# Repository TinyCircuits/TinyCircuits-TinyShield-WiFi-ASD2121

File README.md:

# TinyCircuits TinyShield WiFi Board
# ASD2121 Rev2

These are the design files for the TinyCircuits ASD2121 Rev 2 PCB.  This is a TinyShield board that has a TI CC3000 WiFi module, local power supply and level shifters to connect between the TinyDuino and the WiFi Module. 

Format is in Cadsoft Eagle format - Eagle version 6.2 was used for the original design.

For more infomation on this, check out the product page at Tiny-Circuits.com:  https://tiny-circuits.com/tiny-shield-wifi.html

#License:

Design by TinyCircuits.
All design files are released under the Creative Commons Attribution Share-Alike 3.0 License, see the following link for details: http://creativecommons.org/licenses/by-sa/3.0

All text above must be included in any redistribution or derived design

This project uses designs and concepts developed as part of the Arduino project and the LilyPad project.  The TinyCircuits design files themselves (schematics, PCB and libraries) are not directly derived from these works' design files and have been created new, however the concepts and basic architecture behind the TinyDuino and TinyLily products are derived and we thank the hard work of the organizations below for their contributions to open-source hardware:
  
Original Arduino Uno Design by Team Arduino

LilyPad Arduino Design by Leah Buechley and Sparkfun Electronics

Please support the open-source hardware community

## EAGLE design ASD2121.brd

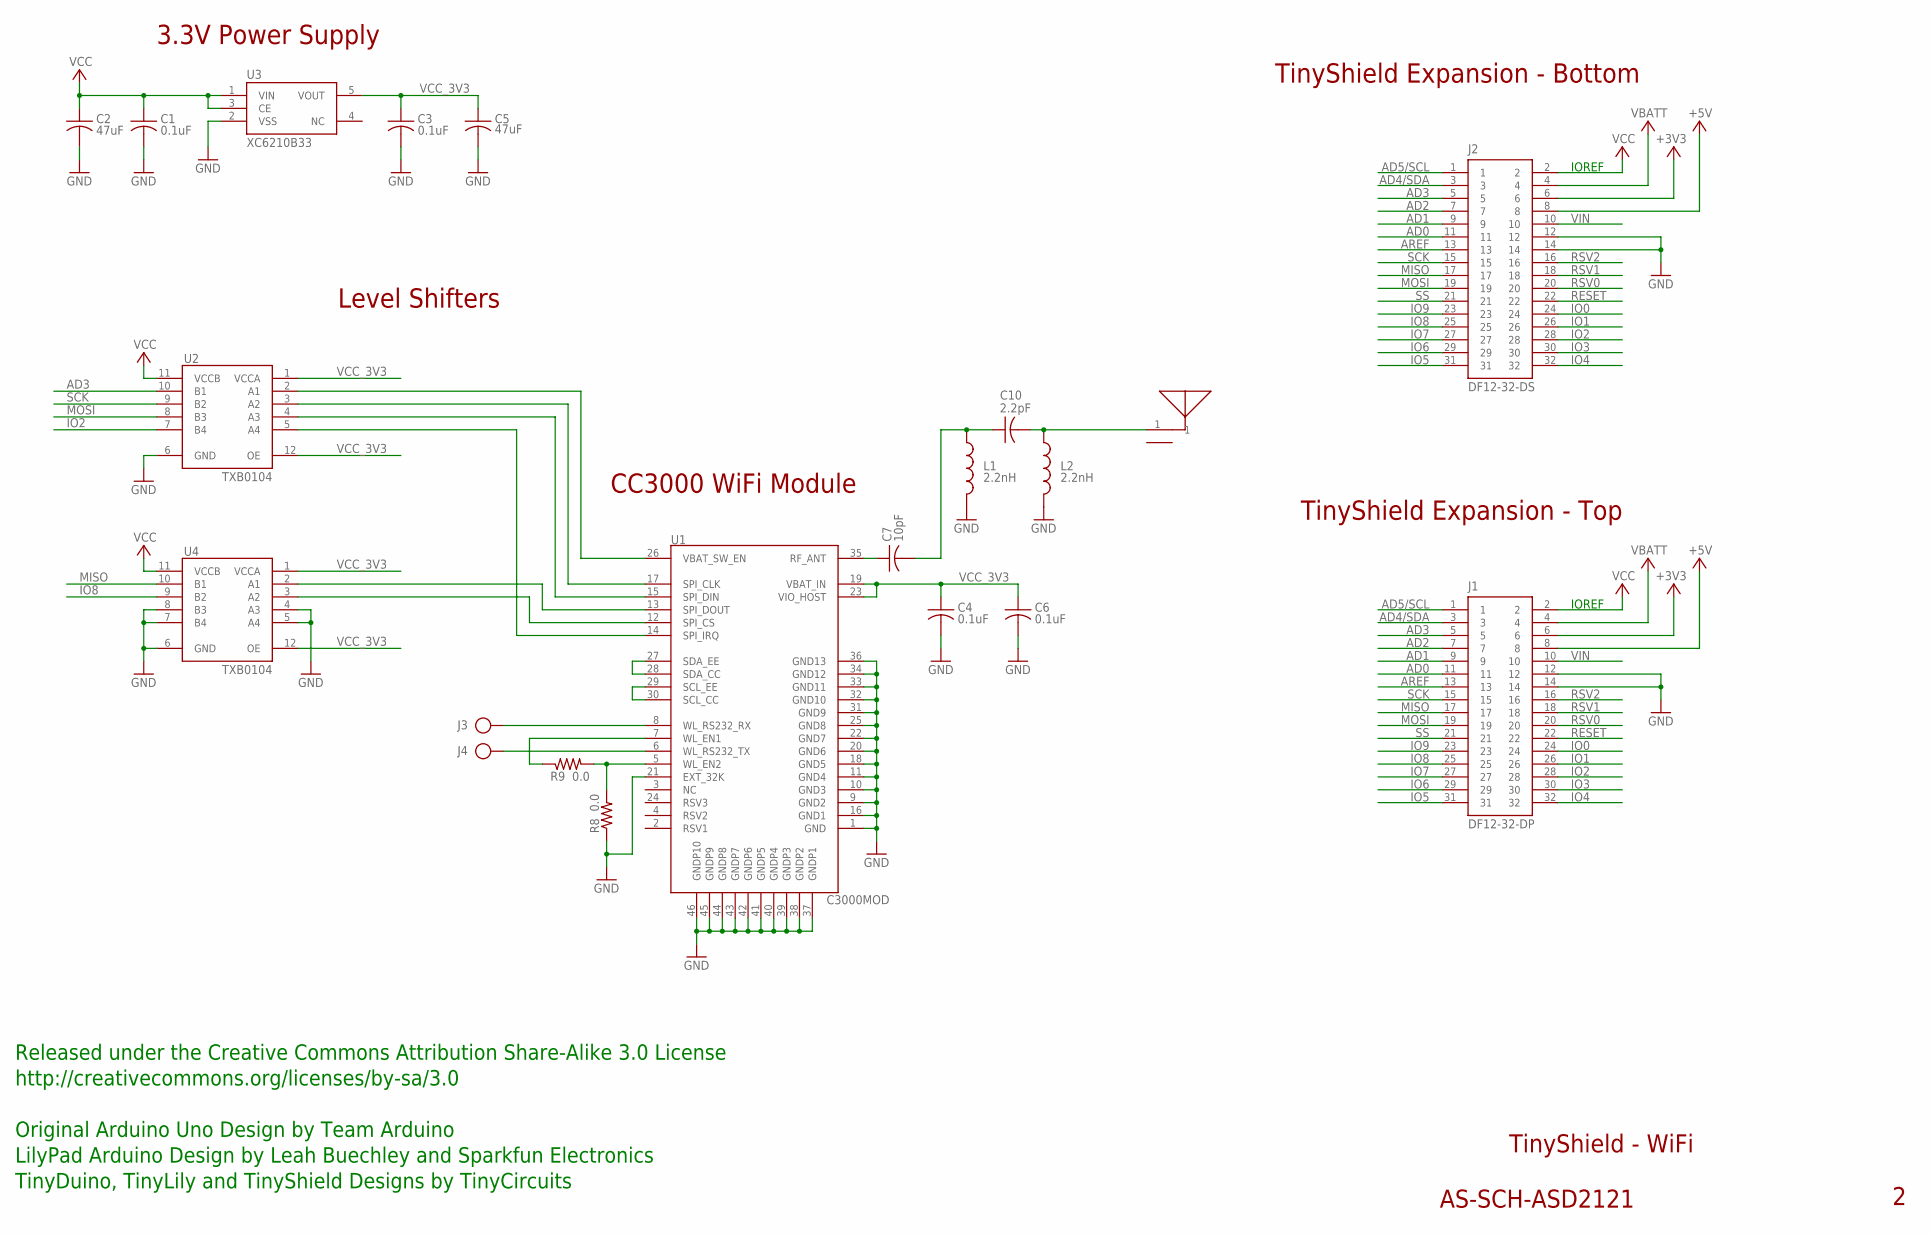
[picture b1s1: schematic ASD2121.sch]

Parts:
ANT1: AS-ITM-00082; 2G4_ANT
C1, C3, C4, C6: 0.1uF; C0402; PARTNO AS-ITM-00008
C2: 47uF; C1206; PARTNUM AS-ITM-00049
C5: 47uF; C1206
C7: 10pF; C0402; PARTNO AS-ITM-00107
C10: 2.2pF; C0402; PARTNO AS-ITM-00106
J1: DF12-32-DP; PARTNO AS-ITM-00015
J2: DF12-32-DS; PARTNO AS-ITM-00012
J3, J4: PIN_1X.1"SQ_PAD; TEST_POINT
L1, L2: 2.2nH; C0402; PARTNO AS-ITM-00108
R8: 0.0; 0402
R9: 0.0; 0402_SHORT
U1: C3000MOD; CC3000MOD
U2, U4: TXB0104; UQFN-12
U3: XC6210B33; SOT-25

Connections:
+3V3: J1.6, J2.6
+5V: J1.8, J2.8
AD0: J1.11, J2.11
AD1: J1.9, J2.9
AD2: J1.7, J2.7
AD3: J1.5, J2.5, U2.10 (B1)
AD4/SDA: J1.3, J2.3
AD5/SCL: J1.1, J2.1
AREF: J1.13, J2.13
GND: C1.2, C2.2, C3.2, C4.2, C5.2, C6.2, J1.12, J1.14, J2.12, J2.14, L1.2, L2.2, R8.1, U1.1 (GND), U1.9 (GND2), U1.10 (GND3), U1.11 (GND4), U1.16 (GND1), U1.18 (GND5), U1.20 (GND6), U1.21 (EXT_32K), U1.22 (GND7), U1.25 (GND8), U1.31 (GND9), U1.32 (GND10), U1.33 (GND11), U1.34 (GND12), U1.36 (GND13), U1.37 (GNDP1), U1.38 (GNDP2), U1.39 (GNDP3), U1.40 (GNDP4), U1.41 (GNDP5), U1.42 (GNDP6), U1.43 (GNDP7), U1.44 (GNDP8), U1.45 (GNDP9), U1.46 (GNDP10), U2.6 (GND), U3.2 (VSS), U4.4 (A3), U4.5 (A4), U4.6 (GND), U4.7 (B4), U4.8 (B3)
IO0: J1.24, J2.24
IO1: J1.26, J2.26
IO2: J1.28, J2.28, U2.7 (B4)
IO3: J1.30, J2.30
IO4: J1.32, J2.32
IO5: J1.31, J2.31
IO6: J1.29, J2.29
IO7: J1.27, J2.27
IO8: J1.25, J2.25, U4.9 (B2)
IO9: J1.23, J2.23
MISO: J1.17, J2.17, U4.10 (B1)
MOSI: J1.19, J2.19, U2.8 (B3)
unnamed: U1.29 (SCL_EE), U1.30 (SCL_CC)
unnamed: U1.27 (SDA_EE), U1.28 (SDA_CC)
unnamed: U1.14 (SPI_IRQ), U2.5 (A4)
unnamed: U1.12 (SPI_CS), U4.3 (A2)
unnamed: J3.P$1, U1.8 (WL_RS232_RX)
unnamed: U1.13 (SPI_DOUT), U4.2 (A1)
unnamed: U1.15 (SPI_DIN), U2.4 (A3)
unnamed: J4.P$1, U1.6 (WL_RS232_TX)
unnamed: R8.2, R9.2, U1.5 (WL_EN2)
unnamed: R9.1, U1.7 (WL_EN1)
unnamed: U1.17 (SPI_CLK), U2.3 (A2)
unnamed: U1.26 (VBAT_SW_EN), U2.2 (A1)
unnamed: C7.1, U1.35 (RF_ANT)
unnamed: C7.2, C10.1, L1.1
unnamed: ANT1.1, C10.2, L2.1
RESET: J1.22, J2.22
RSV0: J1.20, J2.20
RSV1: J1.18, J2.18
RSV2: J1.16, J2.16
SCK: J1.15, J2.15, U2.9 (B2)
SS: J1.21, J2.21
VBATT: J1.4, J2.4
VCC: C1.1, C2.1, J1.2, J2.2, U2.11 (VCCB), U3.1 (VIN), U3.3 (CE), U4.11 (VCCB)
VCC_3V3: C3.1, C4.1, C5.1, C6.1, U1.19 (VBAT_IN), U1.23 (VIO_HOST), U2.1 (VCCA), U2.12 (OE), U3.5 (VOUT), U4.1 (VCCA), U4.12 (OE)
VIN: J1.10, J2.10

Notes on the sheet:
TinyShield Expansion - Bottom
TinyShield - WiFi
AS-SCH-ASD2121
TinyShield Expansion - Top
IOREF
Released under the Creative Commons Attribution Share-Alike 3.0 License
http://creativecommons.org/licenses/by-sa/3.0
LilyPad Arduino Design by Leah Buechley and Sparkfun Electronics
TinyDuino, TinyLily and TinyShield Designs by TinyCircuits
Original Arduino Uno Design by Team Arduino
3.3V Power Supply
CC3000 WiFi Module
Level Shifters

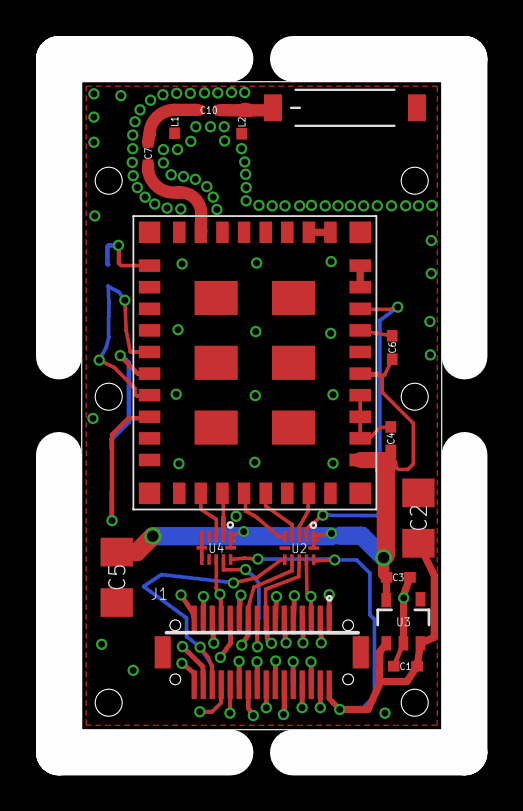
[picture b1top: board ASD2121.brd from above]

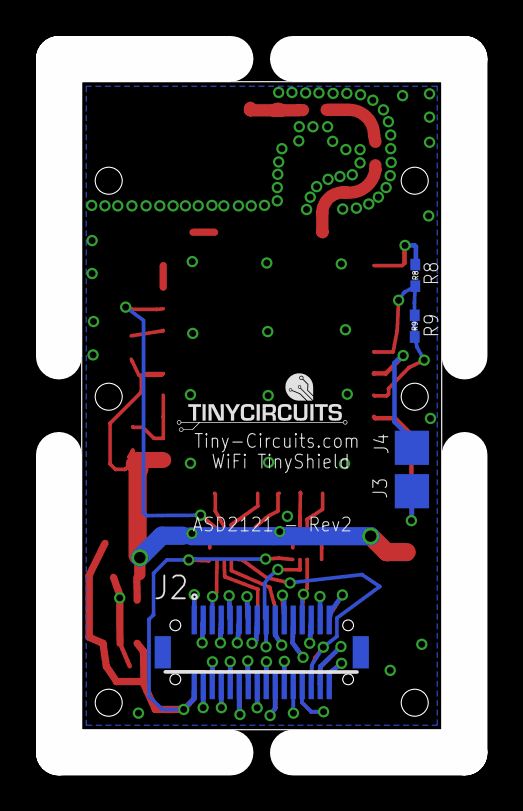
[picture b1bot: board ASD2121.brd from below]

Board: 2 copper layers, 20.0 x 36.0 mm, 22 parts (5 on the bottom side), 47 nets.

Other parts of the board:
U$1: DOCFIELD-TINYCIRCUITS-PCB

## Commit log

2014-02-13 Fixed link in notes to the correct webpage
2014-08-24 Updated Link
